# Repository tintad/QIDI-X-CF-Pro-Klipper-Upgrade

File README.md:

# QIDI-X-CF-Pro-Klipper-Upgrade
Upgrades for QIDI X-CF Pro for better printing quality

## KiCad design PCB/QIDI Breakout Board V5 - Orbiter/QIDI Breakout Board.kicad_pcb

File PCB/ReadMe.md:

PCB is designed with KiCAD 7

V4 is for stock print head
V5 is for Orbiter print head
V4 and V5 are compatible

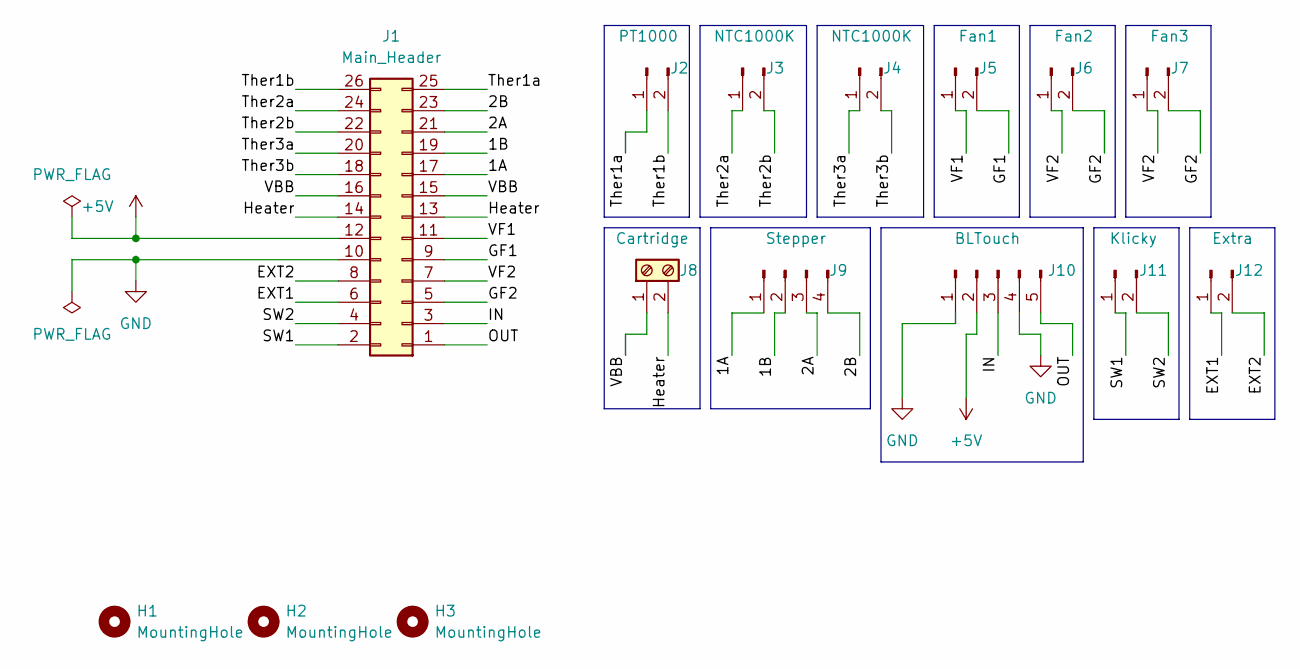
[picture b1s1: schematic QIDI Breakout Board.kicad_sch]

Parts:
H1, H2, H3: MountingHole; MountingHole_3.5mm_Pad
J1: Main_Header; PinHeader_2x13_P2.54mm_Horizontal
J2: PT1000; JST_XH_B2B-XH-A_1x02_P2.50mm_Vertical
J3, J4: NTC1000K; JST_XH_B2B-XH-A_1x02_P2.50mm_Vertical
J5: Fan1; JST_XH_B2B-XH-A_1x02_P2.50mm_Vertical
J6: Fan2; JST_XH_B2B-XH-A_1x02_P2.50mm_Vertical
J7: Fan3; JST_XH_B2B-XH-A_1x02_P2.50mm_Vertical
J8: Cartridge; TerminalBlock_4Ucon_1x02_P3.50mm_Horizontal
J9: Stepper; JST_XH_B4B-XH-A_1x04_P2.50mm_Vertical
J10: BLTouch; JST_XH_B5B-XH-A_1x05_P2.50mm_Vertical
J11: Klicky; JST_XH_B2B-XH-A_1x02_P2.50mm_Vertical
J12: Extra; JST_XH_B2B-XH-A_1x02_P2.50mm_Vertical

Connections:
+5V: J1.12, J10.2
/1A: J1.17, J9.1
/1B: J1.19, J9.2
/2A: J1.21, J9.3
/2B: J1.23, J9.4
/EXT1: J1.6, J12.1
/EXT2: J1.8, J12.2
/GF1: J1.9, J5.2
/GF2: J1.5, J6.2, J7.2
/Heater: J1.13, J1.14, J8.2
/IN: J1.3, J10.3
/OUT: J1.1, J10.5
/SW1: J1.2, J11.1
/SW2: J1.4, J11.2
/Ther1a: J1.25, J2.1
/Ther1b: J1.26, J2.2
/Ther2a: J1.24, J3.1
/Ther2b: J1.22, J3.2
/Ther3a: J1.20, J4.1
/Ther3b: J1.18, J4.2
/VBB: J1.15, J1.16, J8.1
/VF1: J1.11, J5.1
/VF2: J1.7, J6.1, J7.1
GND: J1.10, J10.1, J10.4

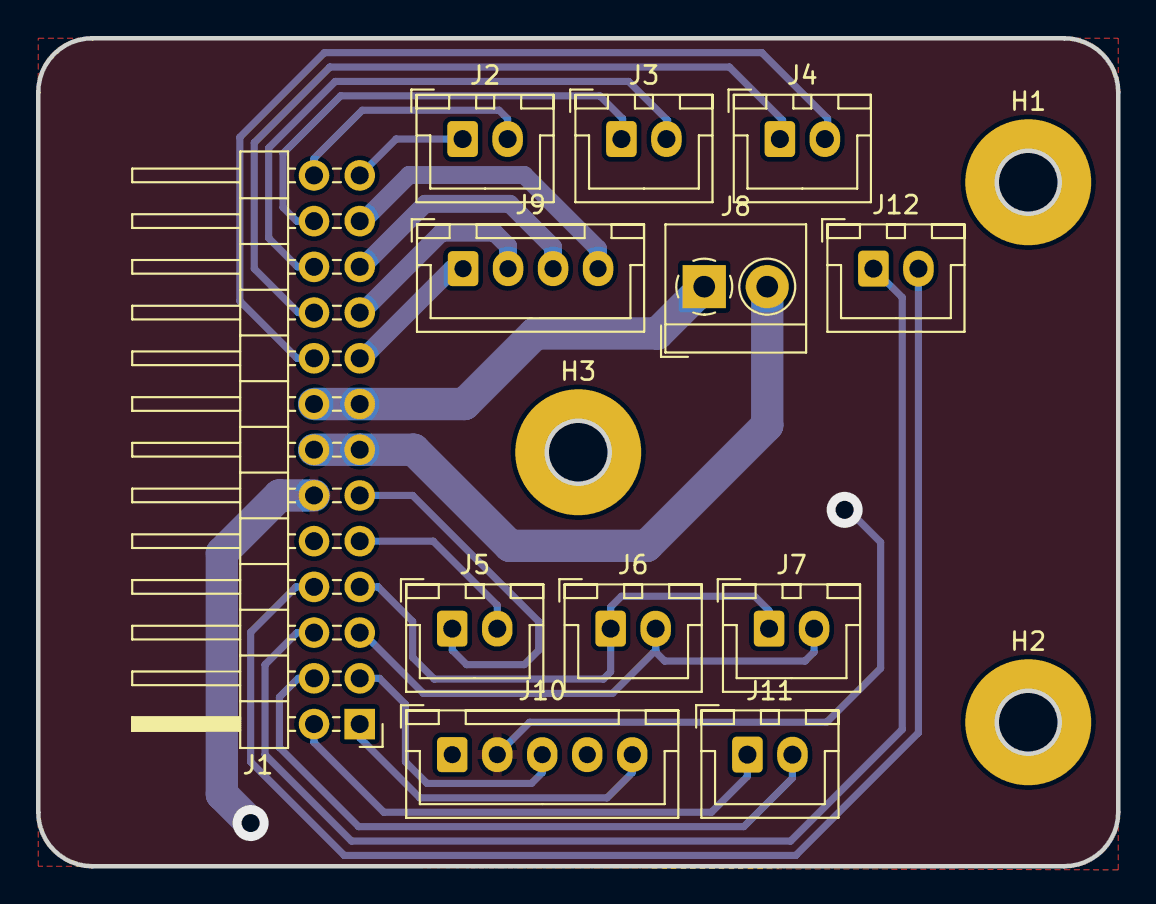
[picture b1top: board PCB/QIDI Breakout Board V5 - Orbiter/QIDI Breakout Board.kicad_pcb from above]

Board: 2 copper layers, 60.0 x 46.0 mm, 15 parts (0 on the bottom side), 24 nets.

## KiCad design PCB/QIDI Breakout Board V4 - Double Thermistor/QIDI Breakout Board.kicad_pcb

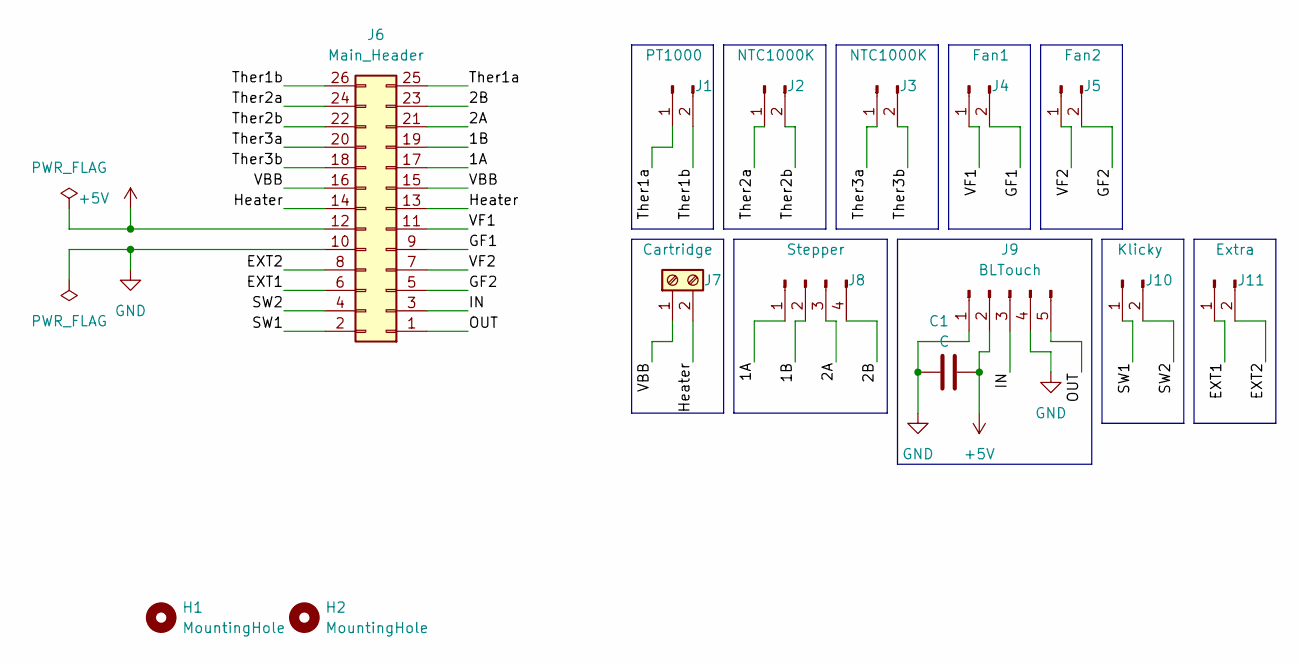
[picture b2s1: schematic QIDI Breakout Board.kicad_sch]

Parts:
C1: C; C_0805_2012Metric_Pad1.15x1.40mm_HandSolder
H1, H2: MountingHole; MountingHole_3.5mm
J1: PT1000; JST_XH_B2B-XH-A_1x02_P2.50mm_Vertical
J2, J3: NTC1000K; JST_XH_B2B-XH-A_1x02_P2.50mm_Vertical
J4: Fan1; JST_XH_B2B-XH-A_1x02_P2.50mm_Vertical
J5: Fan2; JST_XH_B2B-XH-A_1x02_P2.50mm_Vertical
J6: Main_Header; PinHeader_2x13_P2.54mm_Horizontal
J7: Cartridge; TerminalBlock_4Ucon_1x02_P3.50mm_Horizontal
J8: Stepper; JST_XH_B4B-XH-A_1x04_P2.50mm_Vertical
J9: BLTouch; JST_XH_B5B-XH-A_1x05_P2.50mm_Vertical
J10: Klicky; JST_XH_B2B-XH-A_1x02_P2.50mm_Vertical
J11: Extra; JST_XH_B2B-XH-A_1x02_P2.50mm_Vertical

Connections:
+5V: C1.1, J6.12, J9.2
/1A: J6.17, J8.1
/1B: J6.19, J8.2
/2A: J6.21, J8.3
/2B: J6.23, J8.4
/EXT1: J6.6, J11.1
/EXT2: J6.8, J11.2
/GF1: J4.2, J6.9
/GF2: J5.2, J6.5
/Heater: J6.13, J6.14, J7.2
/IN: J6.3, J9.3
/OUT: J6.1, J9.5
/SW1: J6.2, J10.1
/SW2: J6.4, J10.2
/Ther1a: J1.1, J6.25
/Ther1b: J1.2, J6.26
/Ther2a: J2.1, J6.24
/Ther2b: J2.2, J6.22
/Ther3a: J3.1, J6.20
/Ther3b: J3.2, J6.18
/VBB: J6.15, J6.16, J7.1
/VF1: J4.1, J6.11
/VF2: J5.1, J6.7
GND: C1.2, J6.10, J9.1, J9.4

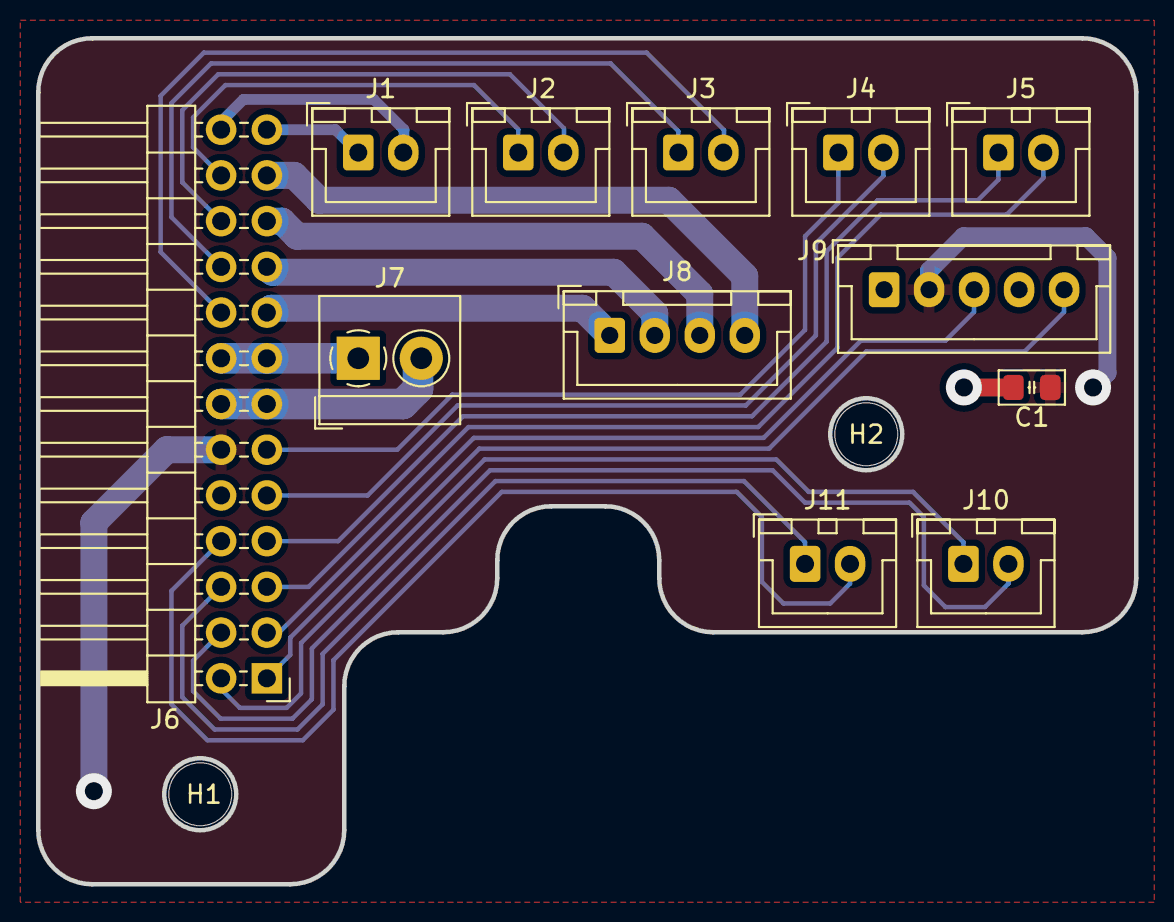
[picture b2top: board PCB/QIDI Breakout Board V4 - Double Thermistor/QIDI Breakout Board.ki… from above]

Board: 2 copper layers, 61.0 x 47.0 mm, 14 parts (0 on the bottom side), 24 nets.

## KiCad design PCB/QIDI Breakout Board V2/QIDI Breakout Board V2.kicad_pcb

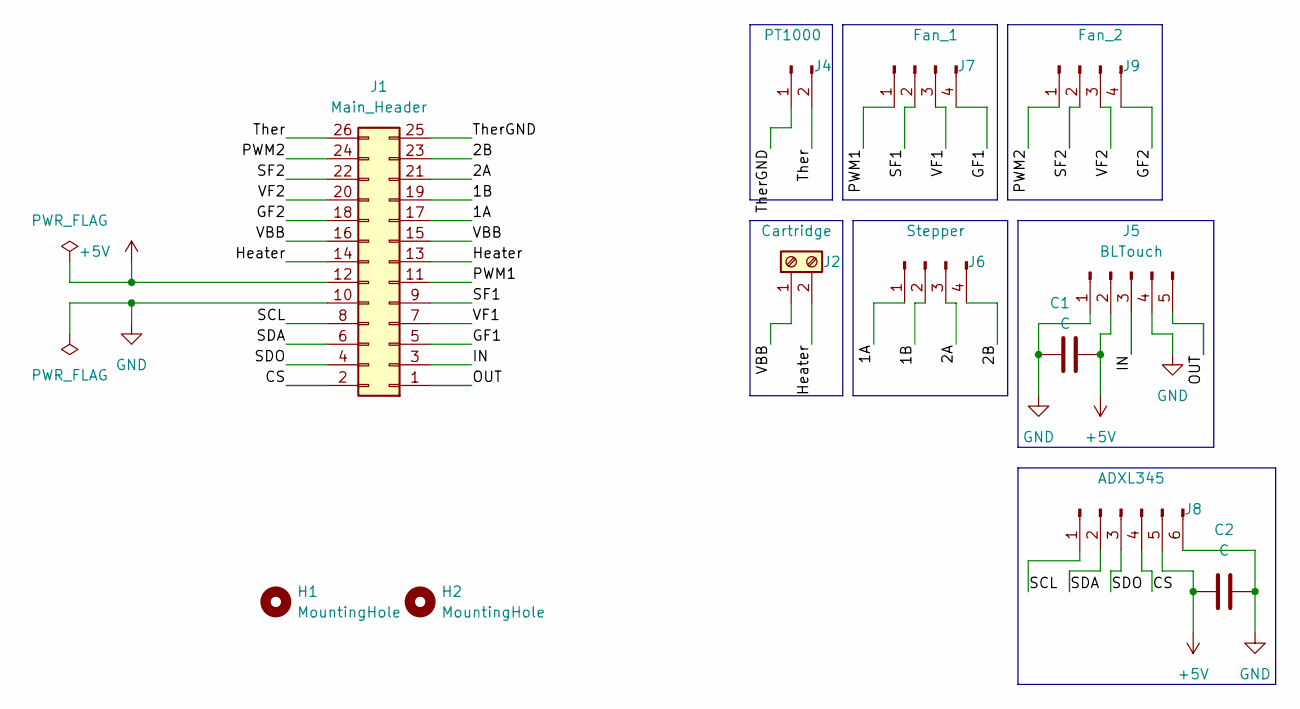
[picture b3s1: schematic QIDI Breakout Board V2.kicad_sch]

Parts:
C1, C2: C; C_0805_2012Metric_Pad1.15x1.40mm_HandSolder
H1, H2: MountingHole; MountingHole_3.5mm
J1: Main_Header; PinHeader_2x13_P2.54mm_Horizontal
J2: Cartridge; TerminalBlock_4Ucon_1x02_P3.50mm_Horizontal
J4: PT1000; JST_XH_B2B-XH-A_1x02_P2.50mm_Vertical
J5: BLTouch; JST_XH_B5B-XH-A_1x05_P2.50mm_Vertical
J6: Stepper; JST_XH_B4B-XH-A_1x04_P2.50mm_Vertical
J7: Fan_1; JST_XH_B4B-XH-A_1x04_P2.50mm_Vertical
J8: ADXL345; JST_XH_B6B-XH-A_1x06_P2.50mm_Vertical
J9: Fan_2; JST_XH_B4B-XH-A_1x04_P2.50mm_Vertical

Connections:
+5V: C1.1, C2.1, J1.12, J5.2, J8.5
/1A: J1.17, J6.1
/1B: J1.19, J6.2
/2A: J1.21, J6.3
/2B: J1.23, J6.4
/CS: J1.2, J8.4
/GF1: J1.5, J7.4
/GF2: J1.18, J9.4
/Heater: J1.13, J1.14, J2.2
/IN: J1.3, J5.3
/OUT: J1.1, J5.5
/PWM1: J1.11, J7.1
/PWM2: J1.24, J9.1
/SCL: J1.8, J8.1
/SDA: J1.6, J8.2
/SDO: J1.4, J8.3
/SF1: J1.9, J7.2
/SF2: J1.22, J9.2
/Ther: J1.26, J4.2
/TherGND: J1.25, J4.1
/VBB: J1.15, J1.16, J2.1
/VF1: J1.7, J7.3
/VF2: J1.20, J9.3
GND: C1.2, C2.2, J1.10, J5.1, J5.4, J8.6

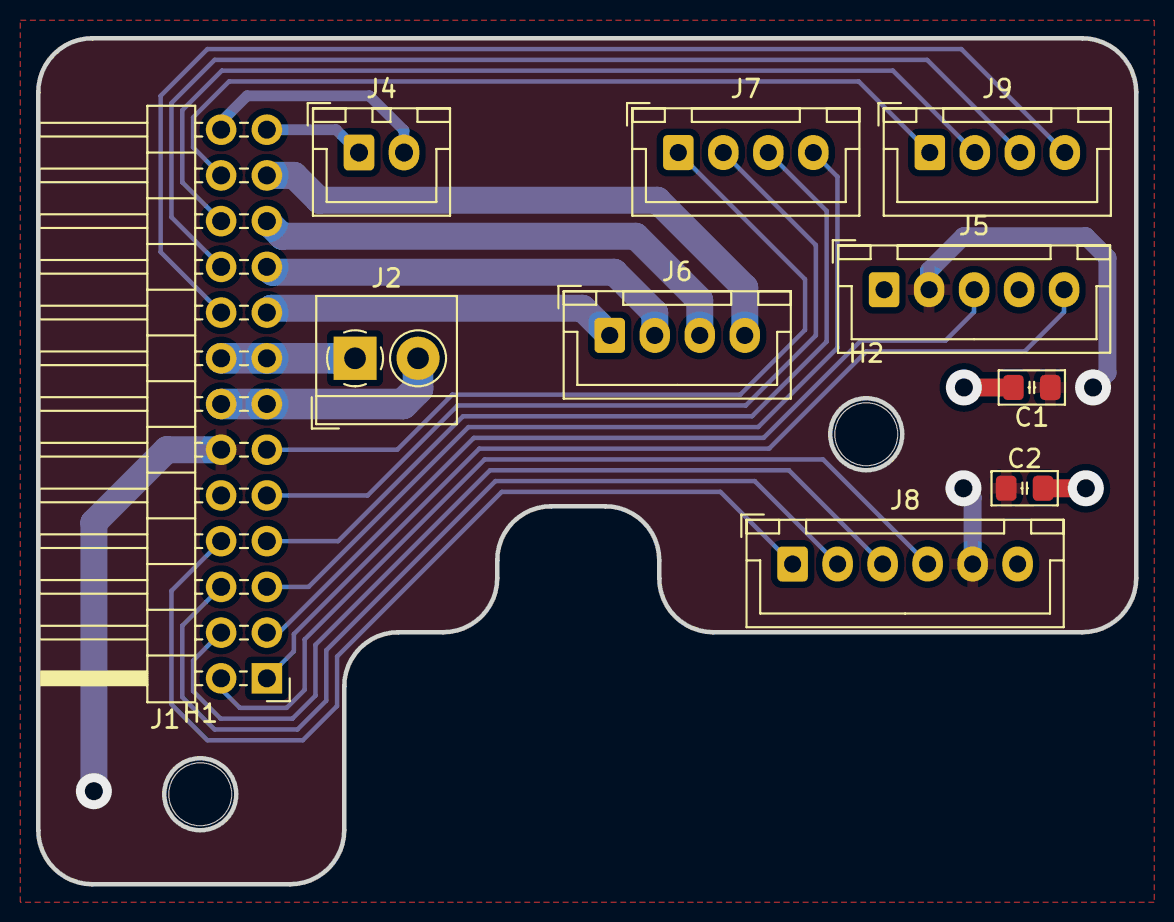
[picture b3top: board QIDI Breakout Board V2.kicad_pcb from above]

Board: 2 copper layers, 61.0 x 47.0 mm, 12 parts (0 on the bottom side), 24 nets.

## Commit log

2023-09-06 Upload CAD
2023-09-06 Config files
2023-09-06 Update CAD
2023-09-06 Change Name
2023-09-06 Breakout Board PCB
2023-09-06 Rename ReadmMe.md to ReadMe.md
2023-09-11 Manta version
2023-09-20 Config 1.0
2023-09-20 Config 2.0
2023-09-21 Bed Power Limit
2023-09-21 Enable Bed Mesh
2023-09-21 Controller Fan
2023-09-21 PID and Mesh Calibrated
2023-09-23 firmware for relay
2023-09-23 Relay Module Function
2023-09-25 Adjust config
2023-10-03 Cura Profile
2023-10-05 Update Cura
2023-10-05 Wiring 1
2023-10-05 BTT Pics
2023-10-06 Not shutdown when upgrade
2023-12-16 Add mainsail.cfg
2024-01-31 Skew Correction, Disable Chamber Heater
2024-01-31 Remesh and Recoordinate
2024-02-05 Update firmware
2024-04-24 Orbiter Extruder
2024-04-24 Orca slicer
2024-05-02 Klipper configs
2024-05-08 Fix Configs
2024-05-08 Test commit
2024-05-08 Update configs
2024-07-30 Update Instruction
2024-08-01 Switch drivers
2024-09-06 Delete
2024-09-07 Revert "Delete"
    This reverts commit baffe55078e83346c7d88b4f420bfc9788477583.
2024-09-07 Revert "Delete"
    This reverts commit 0ea19db52d7dcab0e48b560472aafe59a717d55d.
2024-09-09 Fix structure
2024-09-21 Update Orbiter Profile
2024-09-21 TMC5160 Driver
2024-09-21 Update High Flow Profile
2024-09-21 Update Low Flow Profile
2025-06-20 Disable heater_verify
2025-06-20 Add Arc support
2025-06-20 Fix Arc Support
